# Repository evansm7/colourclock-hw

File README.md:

RGB Colourclock hardware design
===============================

19th March 2018

My Colourclock is a circular wall clock with 60 RGB LEDs.  See <http://www.axio.ms/projects/2018/03/19/Colourclock.html> for information/pictures, and <http://github.com/evansm7/colourclock-fw> for firmware.

This repository contains:

*    Eagle schematic and board files
*    A simple BOM
*    Assembly jig diagram
*    Perl script to automatically create the outline of a single PCB, which is one quarter of a ring of PCBs.  The script also places the 15 RGB LED footprints at the correct locations.

This will hopefully serve as an example for similar designs, and show you how to automate PCB creation using Eagle .brd files (>= version 6).  The workflow was roughly as follows:

*    Create the schematic
*    Create a basic .brd file with instances of LEDs D1 to D15
*    Run this .brd file through the ```mkboard.pl ``` script
*    Tweak the parameters until the size/placement/spacing looks good.

It's possible to change the board outline even after you've routed most of it (and have run out of space...).

* * *

These files are copyright (c) 2014 Matt Evans.  You are permitted to make use of these designs for non-commercial or educational purposes.

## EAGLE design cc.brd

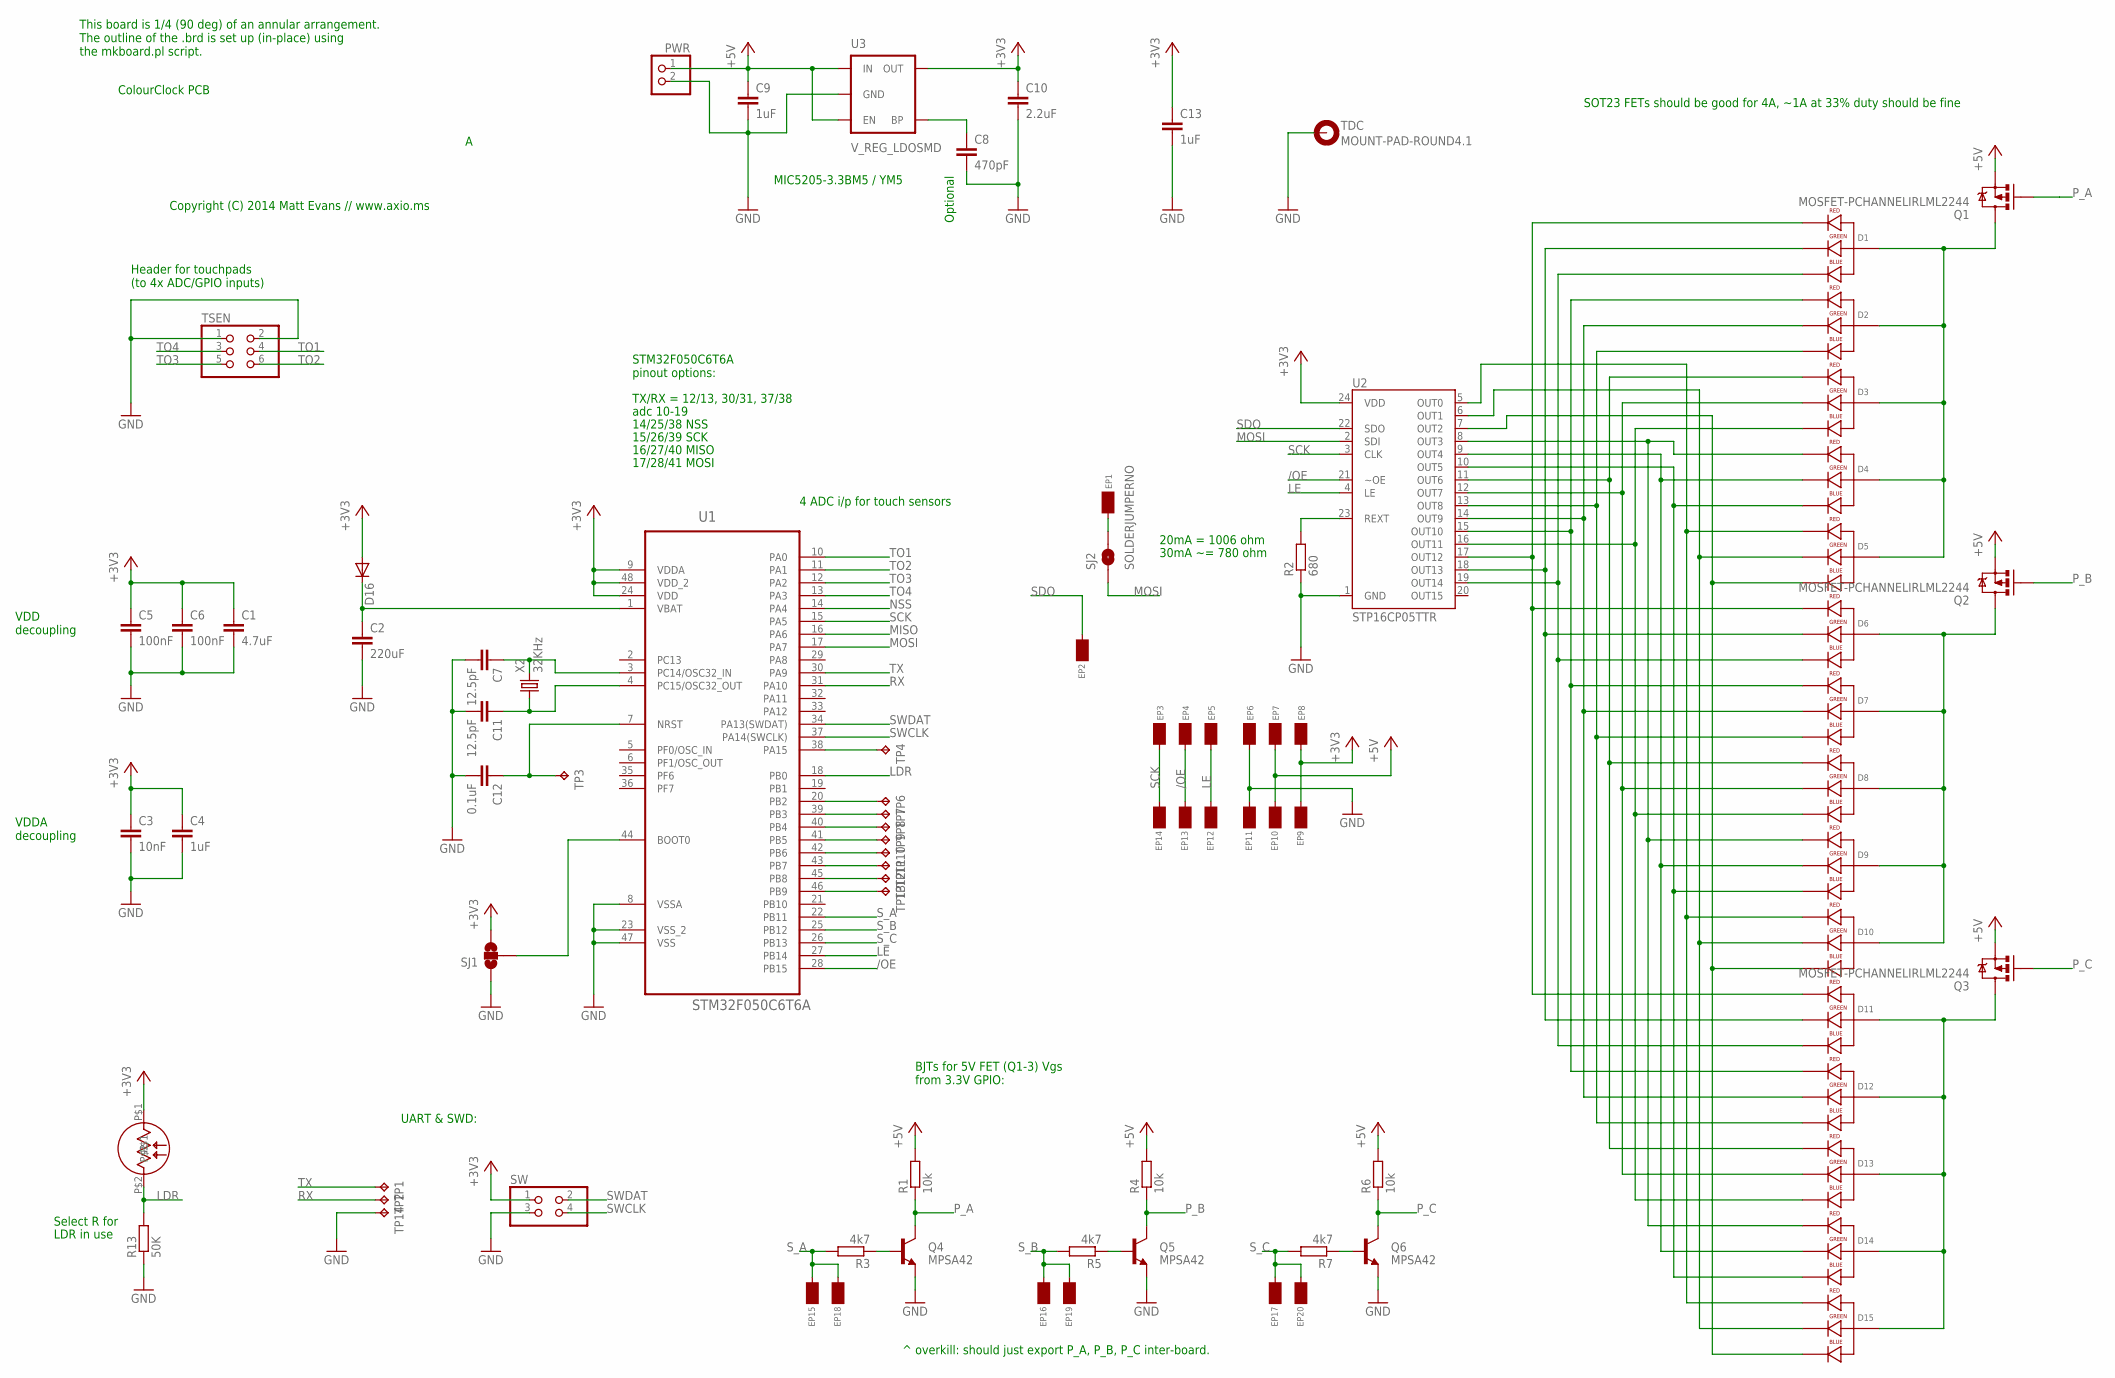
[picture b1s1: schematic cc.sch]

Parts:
C1: 4.7uF; C0603
C2: 220uF; C1210K
C3: 10nF; C0603
C4, C9, C13: 1uF; C0603
C5, C6: 100nF; C0603
C7, C11: 12.5pF; C1005
C8: 470pF; C0603
C10: 2.2uF; C0603
C12: 0.1uF; C1005
D1, D2, D3, D4, D5, D6, D7, D8, D9, D10, D11, D12, D13, D14, D15: LED-RGB-CA-THRUDIFFUSE; LED-RGB-THRU
D16: DIODESOD; SOD-323
EP1, EP2, EP3, EP4, EP5, EP6, EP7, EP8, EP9, EP10, EP11, EP12, EP13, EP14, EP15, EP16, EP17, EP18, EP19, EP20: EDGEPAD
LDR: VT935G
PWR: PINHD-1X22MM; 1X02-2MM
Q1, Q2, Q3: MOSFET-PCHANNELIRLML2244; SOT23-3
Q4, Q5, Q6: MPSA42; SOT23-3
R1, R4, R6: 10k; R0603
R2: 680; R0603
R3, R5, R7: 4k7; R0603
R13: 50K; R0603
SJ1: SOLDERJUMPER_2WAYS; SJ_3
SJ2: SOLDERJUMPERNO; SJ_2S-NO
SW: PINHD-2X22MM; 2X02-2MM
TDC: MOUNT-PAD-ROUND4.1; 4,1-PAD
TP1, TP2, TP3, TP4, TP6, TP7, TP8, TP9, TP10, TP11, TP12, TP13, TP14: TPTP06R; TP06R
TSEN: PINHD-2X32MM; 2X03-2MM
U1: STM32F050C6T6A; QFP50P900X900X160-48N
U2: STP16CP05TTR; TSSOP24
U3: V_REG_LDOSMD; SOT23-5
X2: 32KHz; TC26V

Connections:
+3V3: C1.1, C3.1, C4.1, C5.1, C6.1, C10.1, C13.1, D16.2 (A), EP8.1, EP9.1, LDR.P$1, SJ1.3, SW.1, U1.9 (VDDA), U1.24 (VDD), U1.48 (VDD_2), U2.24 (VDD), U3.5 (OUT)
+5V: C9.1, EP7.1, EP10.1, PWR.1, Q1.2 (S), Q2.2 (S), Q3.2 (S), R1.2, R4.2, R6.2, U3.1 (IN), U3.3 (EN)
/OE: EP4.1, EP13.1, U1.28 (PB15), U2.21 (~OE)
GND: C1.2, C2.2, C3.2, C4.2, C5.2, C6.2, C7.2, C8.2, C9.2, C10.2, C11.2, C12.2, C13.2, EP6.1, EP11.1, PWR.2, Q4.2 (E), Q5.2 (E), Q6.2 (E), R2.1, R13.1, SJ1.1, SW.3, TDC.B4,1, TP14.TP, TSEN.1, TSEN.2, U1.8 (VSSA), U1.23 (VSS_2), U1.47 (VSS), U2.1 (GND), U3.2 (GND)
LDR: LDR.P$2, R13.2, U1.18 (PB0)
LE: EP5.1, EP12.1, U1.27 (PB14), U2.4 (LE)
MISO: U1.16 (PA6)
MOSI: SJ2.1, U1.17 (PA7), U2.2 (SDI)
unnamed: D1.1 (RED_CATHODE), D6.1 (RED_CATHODE), D11.1 (RED_CATHODE), U2.17 (OUT12)
unnamed: D1.3 (GREEN_CATHODE), D6.3 (GREEN_CATHODE), D11.3 (GREEN_CATHODE), U2.18 (OUT13)
unnamed: D1.4 (BLUE_CATHODE), D6.4 (BLUE_CATHODE), D11.4 (BLUE_CATHODE), U2.19 (OUT14)
unnamed: D2.1 (RED_CATHODE), D7.1 (RED_CATHODE), D12.1 (RED_CATHODE), U2.15 (OUT10)
unnamed: D2.3 (GREEN_CATHODE), D7.3 (GREEN_CATHODE), D12.3 (GREEN_CATHODE), U2.14 (OUT9)
unnamed: D2.4 (BLUE_CATHODE), D7.4 (BLUE_CATHODE), D12.4 (BLUE_CATHODE), U2.13 (OUT8)
unnamed: D3.1 (RED_CATHODE), D8.1 (RED_CATHODE), D13.1 (RED_CATHODE), U2.11 (OUT6)
unnamed: D3.3 (GREEN_CATHODE), D8.3 (GREEN_CATHODE), D13.3 (GREEN_CATHODE), U2.12 (OUT7)
unnamed: D3.4 (BLUE_CATHODE), D8.4 (BLUE_CATHODE), D13.4 (BLUE_CATHODE), U2.16 (OUT11)
unnamed: D4.1 (RED_CATHODE), D9.1 (RED_CATHODE), D14.1 (RED_CATHODE), U2.8 (OUT3)
unnamed: D4.3 (GREEN_CATHODE), D9.3 (GREEN_CATHODE), D14.3 (GREEN_CATHODE), U2.9 (OUT4)
unnamed: D4.4 (BLUE_CATHODE), D9.4 (BLUE_CATHODE), D14.4 (BLUE_CATHODE), U2.10 (OUT5)
unnamed: D5.1 (RED_CATHODE), D10.1 (RED_CATHODE), D15.1 (RED_CATHODE), U2.5 (OUT0)
unnamed: D5.3 (GREEN_CATHODE), D10.3 (GREEN_CATHODE), D15.3 (GREEN_CATHODE), U2.6 (OUT1)
unnamed: D5.4 (BLUE_CATHODE), D10.4 (BLUE_CATHODE), D15.4 (BLUE_CATHODE), U2.7 (OUT2)
unnamed: C7.1, U1.3 (PC14/OSC32_IN), X2.2
unnamed: C11.1, U1.4 (PC15/OSC32_OUT), X2.1
unnamed: R2.2, U2.23 (REXT)
unnamed: C2.1, D16.1 (C), U1.1 (VBAT)
unnamed: TP8.TP, U1.40 (PB4)
unnamed: TP7.TP, U1.39 (PB3)
unnamed: EP1.1, SJ2.2
unnamed: TP6.TP, U1.20 (PB2)
unnamed: Q5.1 (B), R5.1
unnamed: C12.1, TP3.TP, U1.7 (NRST)
unnamed: Q4.1 (B), R3.1
unnamed: D11.2 (ANODE), D12.2 (ANODE), D13.2 (ANODE), D14.2 (ANODE), D15.2 (ANODE), Q3.3 (D)
unnamed: D6.2 (ANODE), D7.2 (ANODE), D8.2 (ANODE), D9.2 (ANODE), D10.2 (ANODE), Q2.3 (D)
unnamed: D1.2 (ANODE), D2.2 (ANODE), D3.2 (ANODE), D4.2 (ANODE), D5.2 (ANODE), Q1.3 (D)
unnamed: C8.1, U3.4 (BP)
unnamed: TP4.TP, U1.38 (PA15)
unnamed: SJ1.2, U1.44 (BOOT0)
unnamed: Q6.1 (B), R7.1
unnamed: TP9.TP, U1.41 (PB5)
unnamed: TP10.TP, U1.42 (PB6)
unnamed: TP11.TP, U1.43 (PB7)
unnamed: TP12.TP, U1.45 (PB8)
unnamed: TP13.TP, U1.46 (PB9)
NSS: U1.14 (PA4)
P_A: Q1.1 (G), Q4.3 (C), R1.1
P_B: Q2.1 (G), Q5.3 (C), R4.1
P_C: Q3.1 (G), Q6.3 (C), R6.1
RX: TP2.TP, U1.31 (PA10)
SCK: EP3.1, EP14.1, U1.15 (PA5), U2.3 (CLK)
SDO: EP2.1, U2.22 (SDO)
SWCLK: SW.4, U1.37 (PA14(SWCLK))
SWDAT: SW.2, U1.34 (PA13(SWDAT))
S_A: EP15.1, EP18.1, R3.2, U1.22 (PB11)
S_B: EP16.1, EP19.1, R5.2, U1.25 (PB12)
S_C: EP17.1, EP20.1, R7.2, U1.26 (PB13)
TO1: TSEN.4, U1.10 (PA0)
TO2: TSEN.6, U1.11 (PA1)
TO3: TSEN.5, U1.12 (PA2)
TO4: TSEN.3, U1.13 (PA3)
TX: TP1.TP, U1.30 (PA9)

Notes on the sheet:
Select R for
LDR in use
20mA = 1006 ohm
30mA ~= 780 ohm
Optional
VDDA decoupling
VDD decoupling
17/28/41 MOSI
16/27/40 MISO
15/26/39 SCK
14/25/38 NSS
adc 10-19
TX/RX = 12/13, 30/31, 37/38
SOT23 FETs should be good for 4A, ~1A at 33% duty should be fine
4 ADC i/p for touch sensors
Header for touchpads (to 4x ADC/GPIO inputs)
STM32F050C6T6A pinout options:
UART & SWD:
BJTs for 5V FET (Q1-3) Vgs from 3.3V GPIO:
ColourClock PCB
This board is 1/4 (90 deg) of an annular arrangement. The outline of the .brd is set up (in-place) using the mkboard.pl script.
MIC5205-3.3BM5 / YM5
^ overkill: should just export P_A, P_B, P_C inter-board.
Copyright (C) 2014 Matt Evans // www.axio.ms

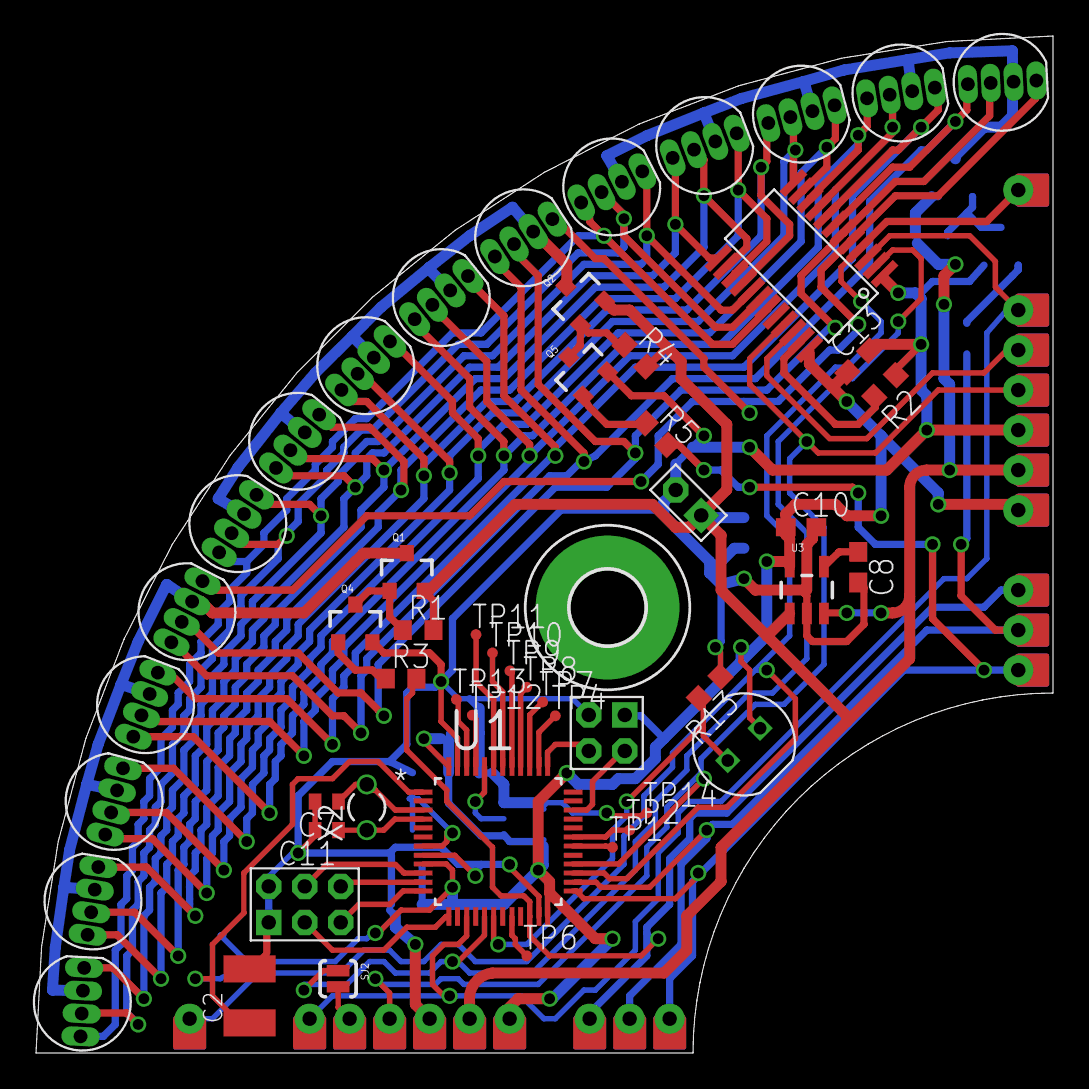
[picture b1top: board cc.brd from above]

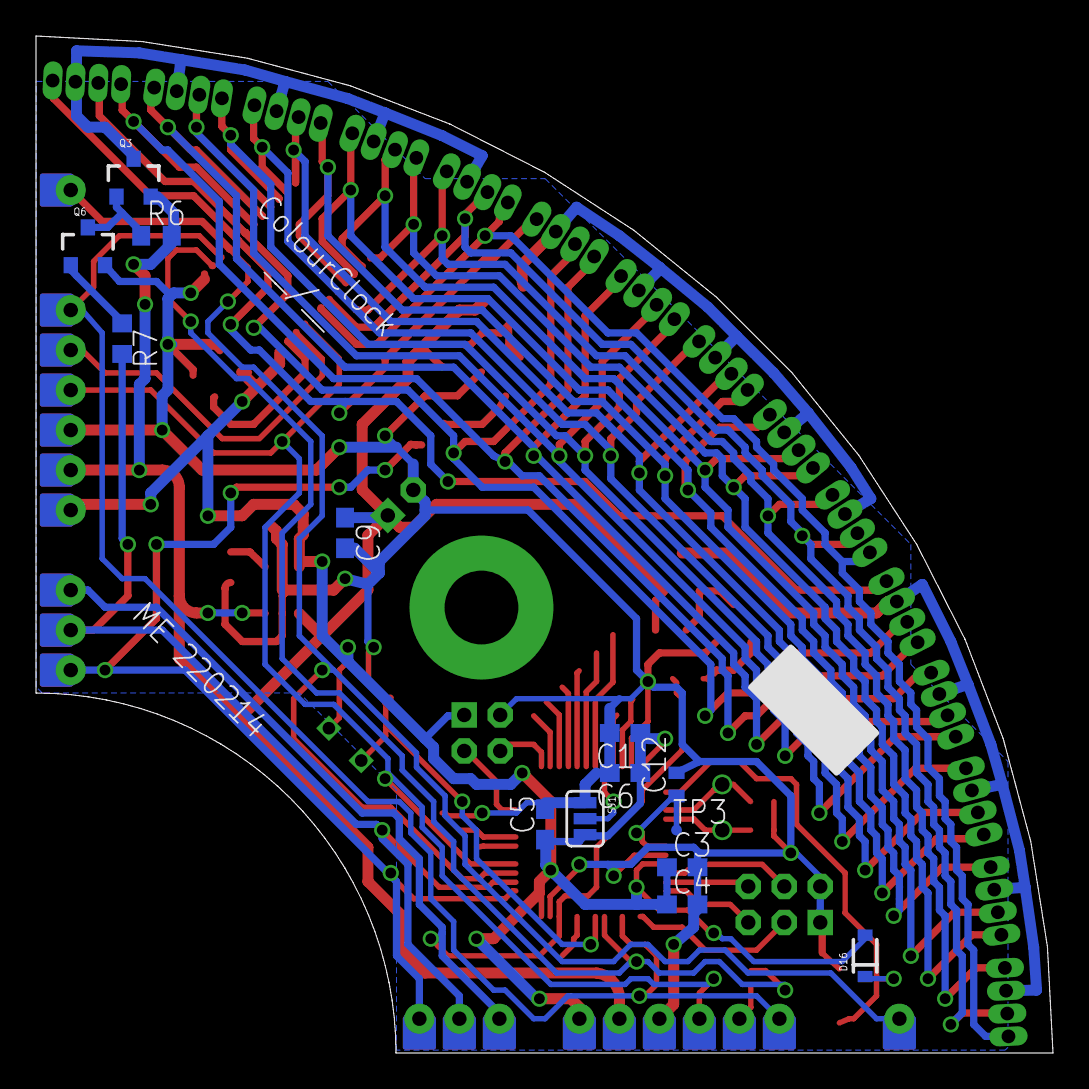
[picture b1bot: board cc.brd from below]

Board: 4 copper layers, 56.5 x 56.5 mm, 87 parts (14 on the bottom side), 61 nets.

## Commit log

2018-03-18 Initial commit:
    RGB Colourclock schematic and board layout, revision A.
    This board has been built/verified working (but see errata.txt).
2018-03-19 Updated README with link to project page

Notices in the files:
parts and their libraries:
SparkFun-DiscreteSemi: Licensing: CC v3.0 Share-Alike You are welcome to use this library for commercial purposes.
